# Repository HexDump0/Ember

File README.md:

[![Contributors][contributors-shield]][contributors-url]
[![Forks][forks-shield]][forks-url]
[![Stargazers][stars-shield]][stars-url]
[![Issues][issues-shield]][issues-url]

<br />
<div align="center">
<h3 align="center">Ember</h3>

  <p align="center">
    A cheap, diy model rocket with a flight recorder and everything else you would need to fy it
    <br />
    <a href="https://github.com/HexDump0/Ember"><strong>See the guide »</strong></a>
    <br />
    <br />
    <a href="#">Video (Soon)</a>
    &middot;
    <a href="https://github.com/HexDump0/Ember/tree/master/models">Models</a>
    &middot;
    <a href="https://github.com/HexDump0/Ember/tree/master/gerber">Gerber</a>
    &middot;
    <a href="https://github.com/HexDump0/Ember/releases/tag/v1.0">Firmware</a>
  </p>
</div>

## About The Project

Ember is a diy, cheap and open source model rocket along with everything you would need to launch it + detailed guides on actually building it

<p align="right">(<a href="#readme-top">back to top</a>)</p>

## Images

|  | | |
|:---------------:|:------------------:|:---------:|
| <br><sub>Flight Recorder</sub> | <br><sub>Flight Recorder 3D</sub> | <br><sub>Dashboard</sub> |
| <br><sub>Launch Controller</sub> | <br><sub>Launch Controller 3D</sub> |  |

## Guide

### 3D Printing
A few of the important parts of the rocket are 3d printed, you could get away with using PLA for them but ABS is better if you have it.

Recommended print settings:
- Layer heigh  -> 0.2mm
- Wall lines -> 5
- Infill -> Gyroid 40%
- Top & Bottom layers -> 4

### Nose cone
Add normal supports for the lip in the shoulder. It should come off easily

### Fins x4
Print it with the fin tab facing the bed and with the `Seam corner preference` set to `Hide Seam`

### Launch lugs x2
### Engine block
### Centering rings x2
### Launch Controller Body/Panel
### Launch Pad Leg/Body

You can just print these with the recommenced settings 

### PCB/Electronics

The gerber files for both the launch controller and flight recorder are available [here](https://github.com/HexDump0/Ember/tree/master/gerber)

Make sure you would a bit of 22 AWG wires at hand for the panel lights and switches

The Battery is meant to be charged on the bench and then soldered on to the flight recorder

(More detailed guide will come once I get my PCBs)

### Flashing the firmware

You need [`esptool`](https://docs.espressif.com/projects/esptool/). Install it using

```sh
pip install --user esptool
```

Plug the Super Mini into USB. It should show up as `/dev/ttyACM0` on Linux,
`/dev/tty.usbmodem*` on macOS, and `COMx` on Windows

Flash the [firmware](https://github.com/HexDump0/Ember/releases/tag/v1.0) using

```sh
esptool --chip esp32c3 --port /dev/ttyACM0 --baud 460800 \
        write-flash 0x0 ember.bin
```

Once done you should see some logs in serial

```sh
# pick one
idf.py -p /dev/ttyACM0 monitor
miniterm /dev/ttyACM0 115200
screen /dev/ttyACM0 115200
```
```
I (xxx) ember: ember boot
I (xxx) sensors: MPU6050 ready @0x68
I (xxx) sensors: BMP280 ready @0x76 ...
I (xxx) httpd: http server up on :80
I (xxx) wifi_ap: softap up: ssid=ember-XXXXXX ch=1
```

Connect to the open Wi-Fi `ember-XXXXXX` and visit
<http://192.168.4.1> for the dashboard.

## License

Distributed under the Creative Commons Attribution-NonCommercial 4.0. See `LICENSE.md` for more information.

<p align="right">(<a href="#readme-top">back to top</a>)</p>

## Contact

HexDump0 - [@HexDump0](https://x.com/hexdump0) - root@hexdump0.pw

Project Link: [https://github.com/HexDump0/Ember](https://github.com/HexDump0/Ember)

<p align="right">(<a href="#readme-top">back to top</a>)</p>

## Acknowledgments

* [SnapEDA](https://www.snapeda.com) for ESP32-C3 SMD Footprint and Symbol
* [UltraLibrarian](https://www.ultralibrarian.com) for FS8205A Footprint and Symbol
* [RabchikEngineer](https://github.com/RabchikEngineer) for KiCad ESP32-C3-SuperMini symbols
* [Ulf Hille](https://grabcad.com/library/esp32c3-supermini-1) for ESP32C3 SuperMini 3D Model
* [Usini](https://ko-fi.com/usini) for Usini Sensors Kicad Schematics and footprints (and associated GrabCAD authors)

<p align="right">(<a href="#readme-top">back to top</a>)</p>

[contributors-shield]: https://img.shields.io/github/contributors/HexDump0/Ember.svg?style=for-the-badge
[contributors-url]: https://github.com/HexDump0/Ember/graphs/contributors
[forks-shield]: https://img.shields.io/github/forks/HexDump0/Ember.svg?style=for-the-badge
[forks-url]: https://github.com/HexDump0/Ember/network/members
[stars-shield]: https://img.shields.io/github/stars/HexDump0/Ember.svg?style=for-the-badge
[stars-url]: https://github.com/HexDump0/Ember/stargazers
[issues-shield]: https://img.shields.io/github/issues/HexDump0/Ember.svg?style=for-the-badge
[issues-url]: https://github.com/HexDump0/Ember/issues
[license-shield]: https://img.shields.io/github/license/HexDump0/Ember.svg?style=for-the-badge
[license-url]: https://github.com/HexDump0/Ember/blob/master/LICENSE.md

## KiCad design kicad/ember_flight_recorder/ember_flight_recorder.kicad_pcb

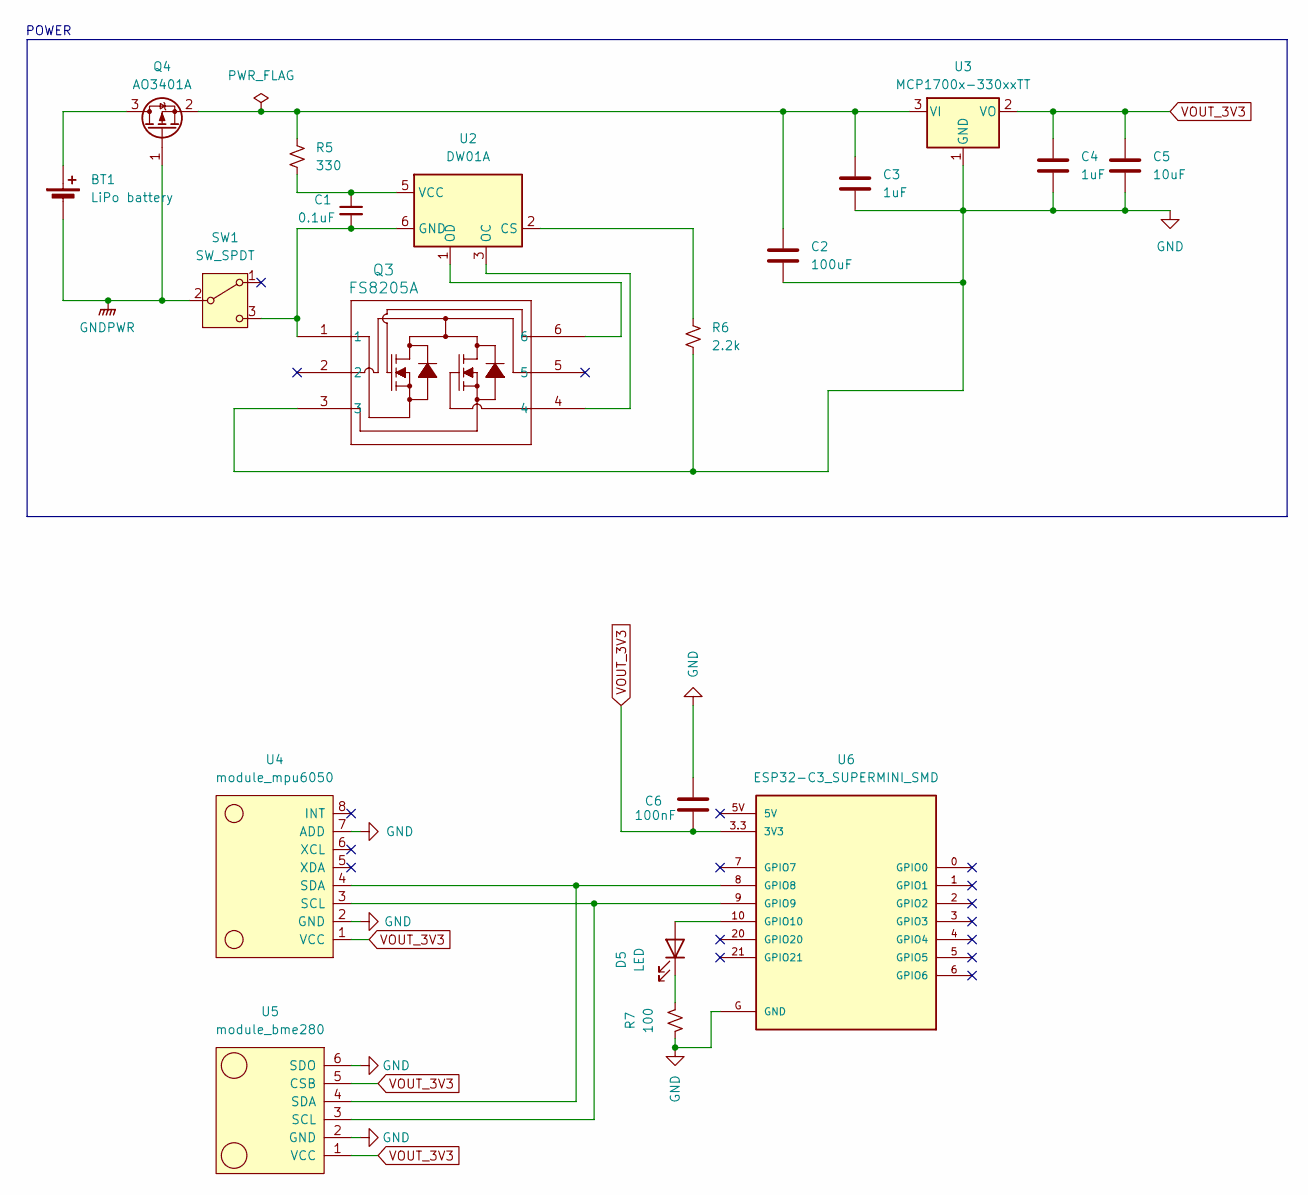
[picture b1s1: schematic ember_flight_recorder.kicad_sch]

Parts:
BT1: LiPo battery; SolderWire-0.75sqmm_1x02_P7mm_D1.25mm_OD3.5mm
C1: 0.1uF; C_1206_3216Metric_Pad1.33x1.80mm_HandSolder
C2: 100uF; C_1206_3216Metric_Pad1.33x1.80mm_HandSolder
C3, C4: 1uF; C_1206_3216Metric_Pad1.33x1.80mm_HandSolder
C5: 10uF; C_1206_3216Metric_Pad1.33x1.80mm_HandSolder
C6: 100nF; C_1206_3216Metric_Pad1.33x1.80mm_HandSolder
D5: LED; LED_1210_3225Metric_Pad1.42x2.65mm_HandSolder
Q3: FS8205A; SOT-23-6L_TCP-M
Q4: AO3401A; SOT-23
R5: 330; R_0805_2012Metric_Pad1.20x1.40mm_HandSolder
R6: 2.2k; R_0805_2012Metric_Pad1.20x1.40mm_HandSolder
R7: 100; R_0805_2012Metric_Pad1.20x1.40mm_HandSolder
SW1: SW_SPDT; SW_Slide-03_Wuerth-WS-SLTV_10x2.5x6.4_P2.54mm
U2: DW01A; SOT-23-6
U3: MCP1700x-330xxTT; SOT-23
U4: module_mpu6050
U5: module_bme280
U6: ESP32-C3_SUPERMINI_SMD; MODULE_ESP32-C3_SUPERMINI

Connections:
GND: C2.2, C3.2, C4.2, C5.2, C6.2, Q3.3, R6.2, R7.2, U3.1 (GND), U4.2 (GND), U4.7 (ADD), U5.2 (GND), U5.6 (SDO), U6.G (GND)
GNDPWR: BT1.2 (-), Q4.1 (G), SW1.2 (B)
unnamed: BT1.1 (+), Q4.3 (D)
unnamed: D5.2 (A), U6.10 (GPIO10)
unnamed: D5.1 (K), R7.1
unnamed: C2.1, C3.1, Q4.2 (S), R5.1, U3.3 (VI)
unnamed: C1.2, Q3.1, SW1.3 (C), U2.6 (GND)
unnamed: R6.1, U2.2 (CS)
unnamed: Q3.4, U2.3 (OC)
unnamed: Q3.6, U2.1 (OD)
unnamed: C1.1, R5.2, U2.5 (VCC)
unnamed: U4.3 (SCL), U5.3 (SCL), U6.9 (GPIO9)
unnamed: U4.4 (SDA), U5.4 (SDA), U6.8 (GPIO8)
VOUT_3V3: C4.1, C5.1, C6.1, U3.2 (VO), U4.1 (VCC), U5.1 (VCC), U5.5 (CSB), U6.3.3 (3V3)

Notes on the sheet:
POWER

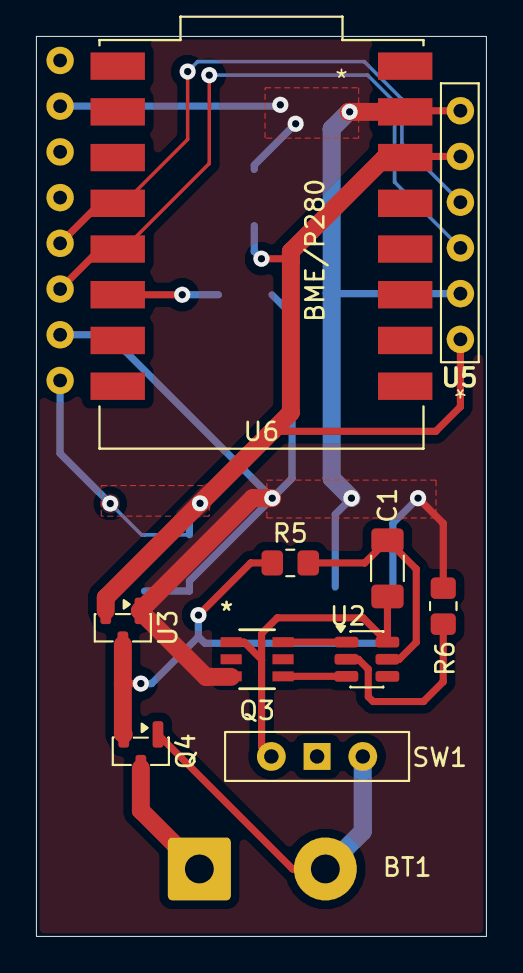
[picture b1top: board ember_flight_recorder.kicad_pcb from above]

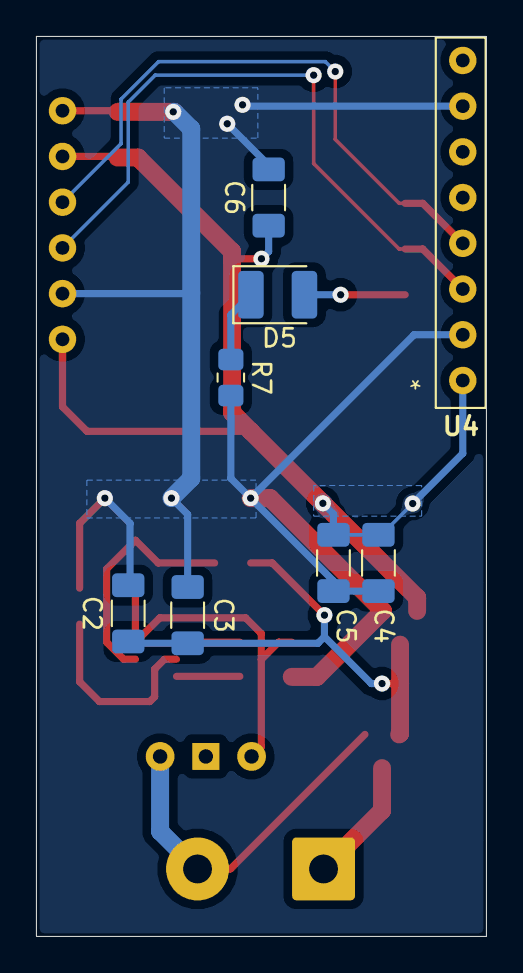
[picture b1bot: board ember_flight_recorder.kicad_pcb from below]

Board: 2 copper layers, 25.0 x 50.0 mm, 19 parts (8 on the bottom side), 14 nets.

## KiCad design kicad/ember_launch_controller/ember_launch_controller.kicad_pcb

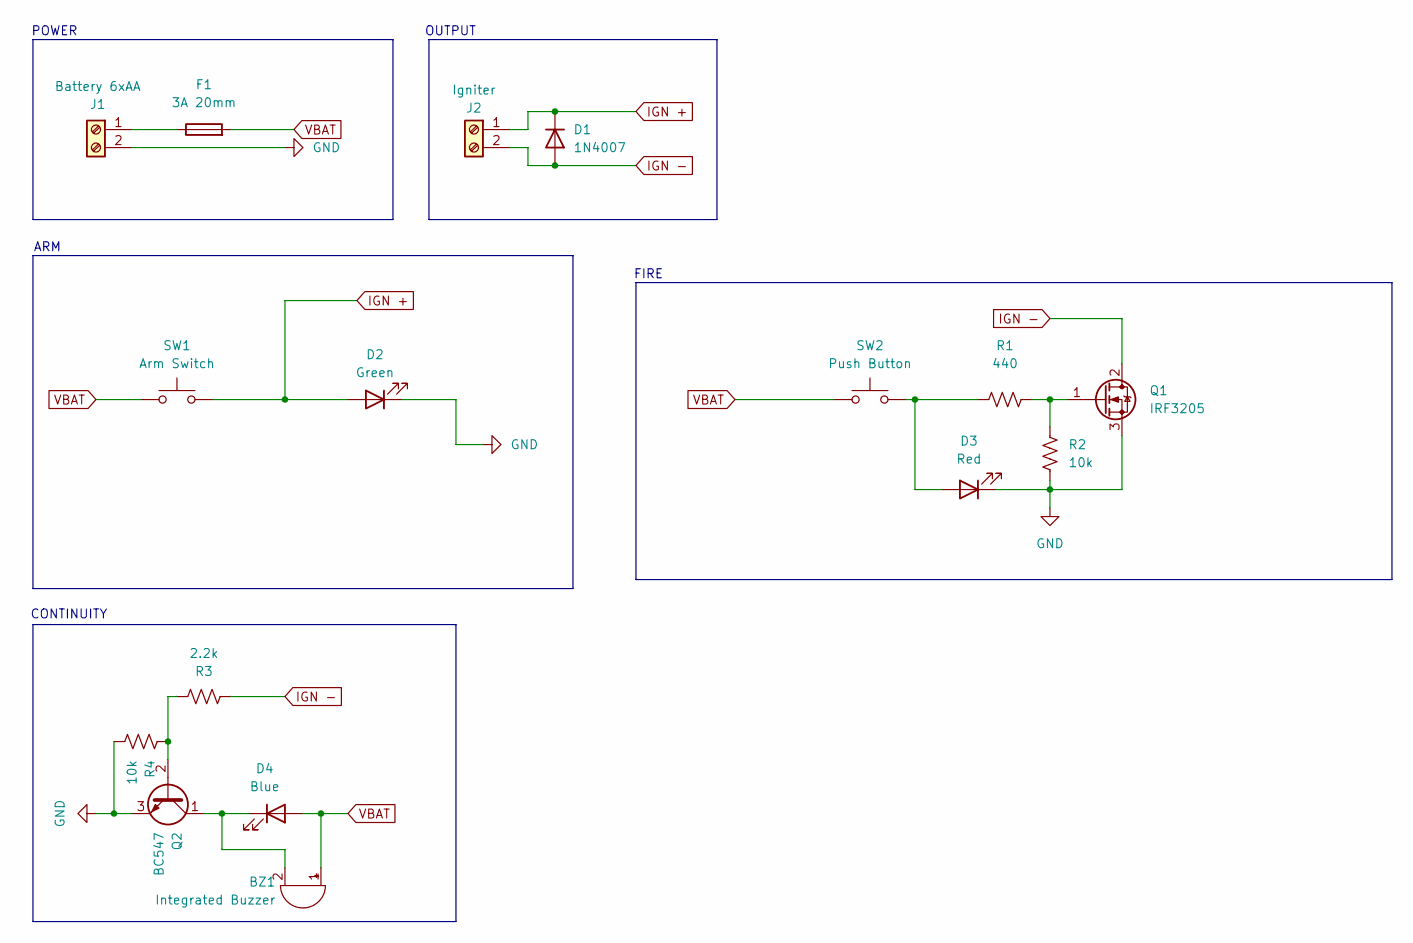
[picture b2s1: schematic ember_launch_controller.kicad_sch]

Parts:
BZ1: Integrated Buzzer; Buzzer_12x9.5RM7.6
D1: 1N4007; D_DO-41_SOD81_P10.16mm_Horizontal
D2: Green; SolderWire-0.75sqmm_1x02_P7mm_D1.25mm_OD3.5mm
D3: Red; SolderWire-0.75sqmm_1x02_P7mm_D1.25mm_OD3.5mm
D4: Blue; SolderWire-0.75sqmm_1x02_P7mm_D1.25mm_OD3.5mm
F1: 3A 20mm; SolderWire-0.75sqmm_1x02_P7mm_D1.25mm_OD3.5mm
J1: Battery 6xAA; TerminalBlock_Phoenix_MKDS-1,5-2_1x02_P5.00mm_Horizontal
J2: Igniter; TerminalBlock_Phoenix_MKDS-1,5-2_1x02_P5.00mm_Horizontal
Q1: IRF3205; TO-220-3_Vertical
Q2: BC547; TO-92_Inline
R1: 440; R_Axial_DIN0207_L6.3mm_D2.5mm_P7.62mm_Horizontal
R2, R4: 10k; R_Axial_DIN0207_L6.3mm_D2.5mm_P7.62mm_Horizontal
R3: 2.2k; R_Axial_DIN0207_L6.3mm_D2.5mm_P7.62mm_Horizontal
SW1: Arm Switch; SolderWire-0.75sqmm_1x02_P7mm_D1.25mm_OD3.5mm
SW2: Push Button; SolderWire-0.75sqmm_1x02_P7mm_D1.25mm_OD3.5mm

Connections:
GND: D2.1 (K), D3.1 (K), J1.2, Q1.3 (S), Q2.3 (E), R2.1, R4.1
IGN +: D1.1 (K), D2.2 (A), J2.1, SW1.2
IGN -: D1.2 (A), J2.2, Q1.2 (D), R3.2
unnamed: BZ1.2 (-), D4.1 (K), Q2.1 (C)
unnamed: D3.2 (A), R1.1, SW2.2
unnamed: F1.1, J1.1
unnamed: Q1.1 (G), R1.2, R2.2
unnamed: Q2.2 (B), R3.1, R4.2
VBAT: BZ1.1 (+), D4.2 (A), F1.2, SW1.1, SW2.1

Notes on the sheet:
OUTPUT
CONTINUITY
POWER
FIRE
ARM

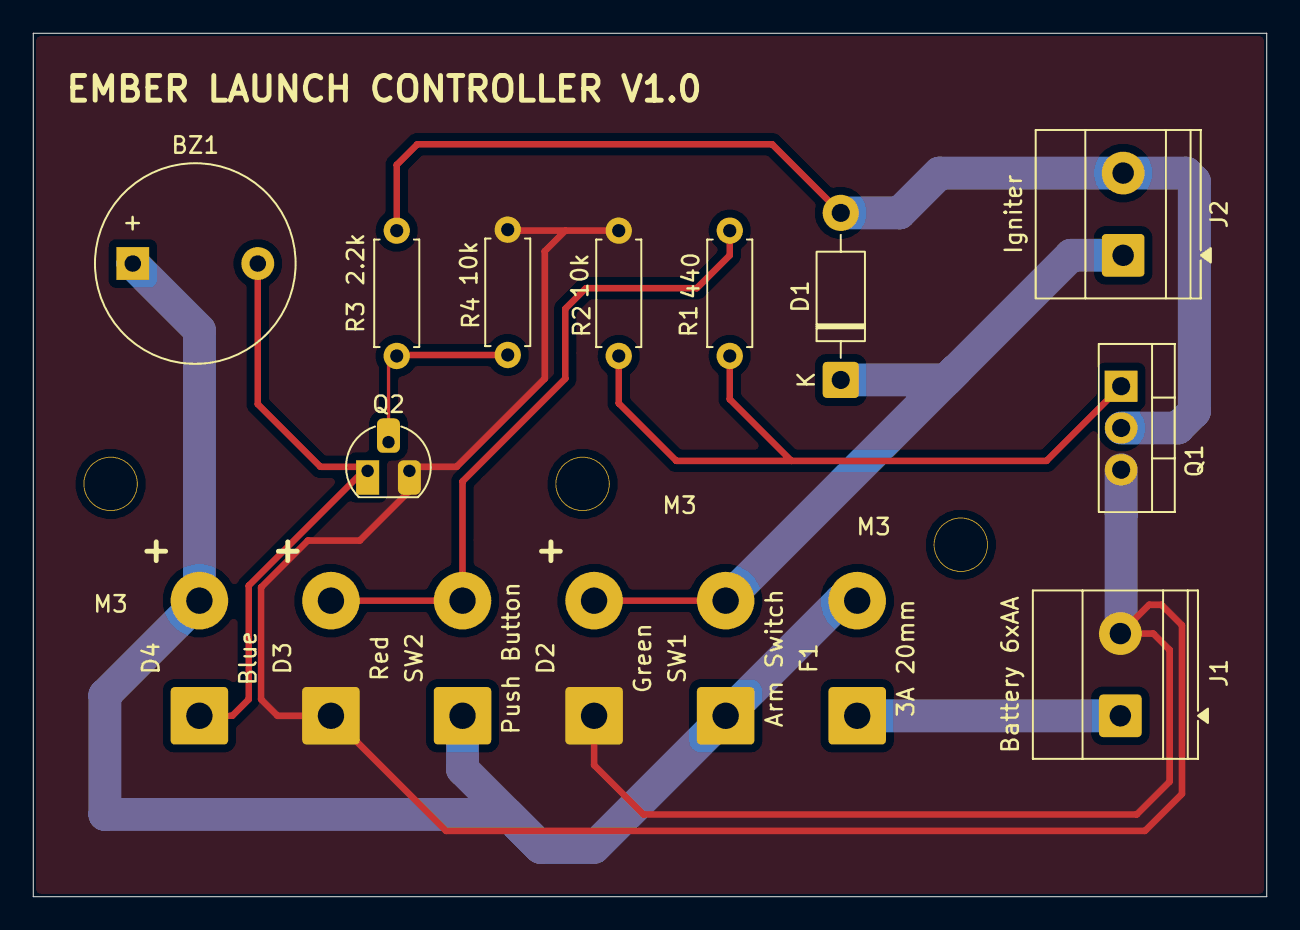
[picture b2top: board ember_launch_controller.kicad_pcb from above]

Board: 2 copper layers, 75.0 x 52.5 mm, 19 parts (0 on the bottom side), 9 nets.

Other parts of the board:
M3, M3#2, M3#3: MountingHole_3.2mm_M3

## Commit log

2026-04-27 init
2026-05-01 added schematic and pcbs
2026-05-04 added launch controller models
2026-05-04 updated to kicad 10
2026-05-05 added power management for battery
2026-05-05 added sensors
2026-05-05 restructured kicad project
2026-05-05 updated footprint and 3d models
2026-05-05 flight recorder rev1
2026-05-06 flight recorder rev2
2026-05-06 gerber files
2026-05-06 more gerber files
2026-05-07 added fln alignment
2026-05-07 added launch pad
2026-05-07 firmware init
2026-05-07 basic sensor data
2026-05-07 implement logger pipeline
2026-05-07 fake sensor for testing
2026-05-08 added file logging and http server
2026-05-08 added websocket and log download
2026-05-08 removed license shield
2026-05-22 added .step files
